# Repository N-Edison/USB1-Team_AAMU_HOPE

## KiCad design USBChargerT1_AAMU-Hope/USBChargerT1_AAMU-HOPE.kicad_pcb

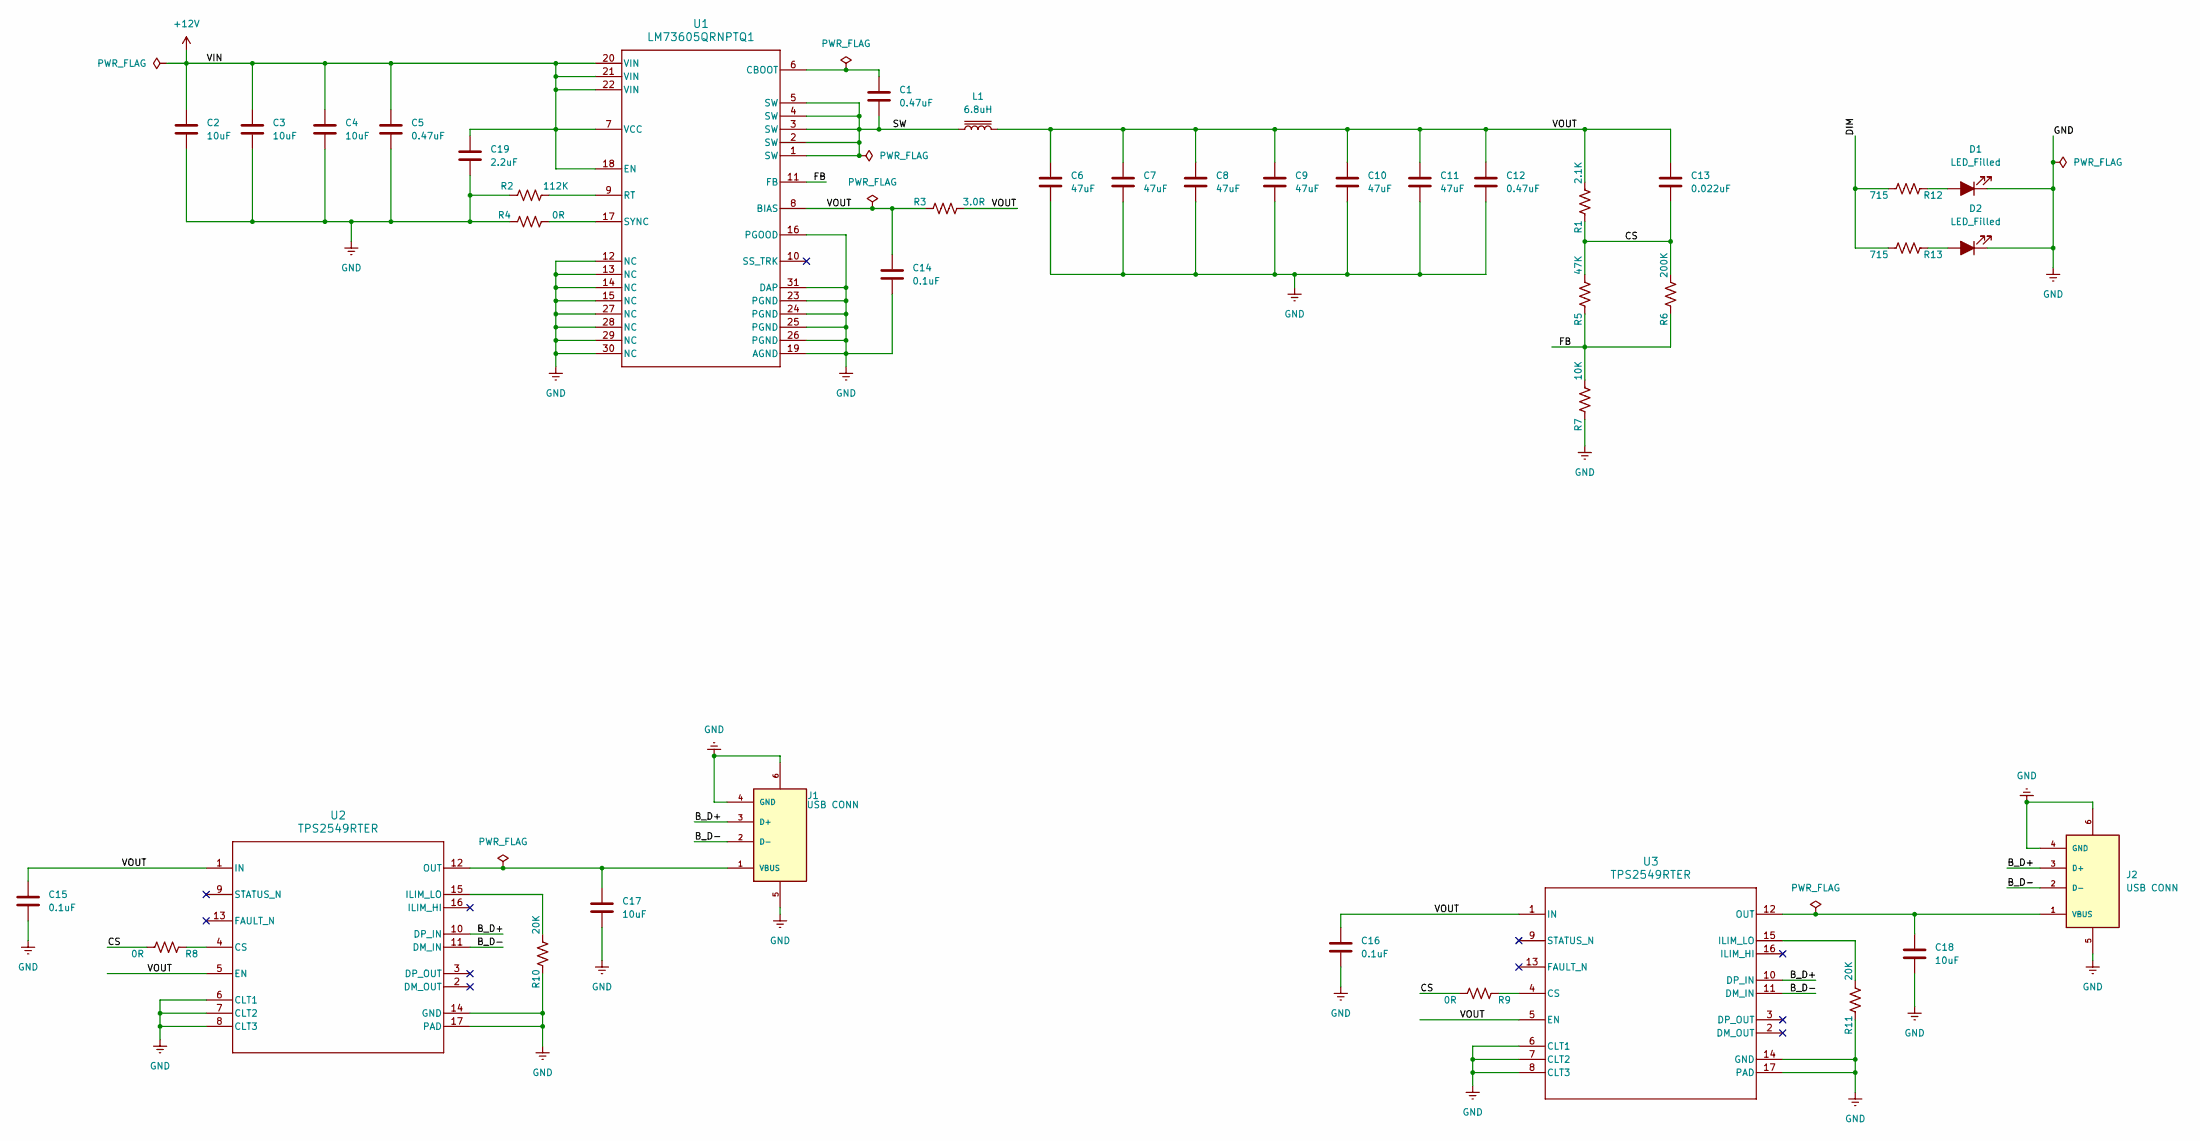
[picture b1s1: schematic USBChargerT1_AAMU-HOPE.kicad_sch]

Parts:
C1, C5, C12: 0.47uF; C_0603_1608Metric_Pad1.08x0.95mm_HandSolder
C2, C3, C4, C17, C18: 10uF; C_0603_1608Metric_Pad1.08x0.95mm_HandSolder
C6, C7, C8, C9, C10, C11: 47uF; C_0603_1608Metric_Pad1.08x0.95mm_HandSolder
C13: 0.022uF; C_0603_1608Metric_Pad1.08x0.95mm_HandSolder
C14, C15, C16: 0.1uF; C_0603_1608Metric_Pad1.08x0.95mm_HandSolder
C19: 2.2uF; C_0603_1608Metric_Pad1.08x0.95mm_HandSolder
D1, D2: LED_Filled; D_0603_1608Metric_Pad1.05x0.95mm_HandSolder
J1, J2: USB CONN; CUI_UJ2-AH-1-SMT; PARTREV 1.01
L1: 6.8uH; L_0603_1608Metric_Pad1.05x0.95mm_HandSolder
R1: 2.1K; R_0603_1608Metric_Pad0.98x0.95mm_HandSolder
R2: 112K; R_0603_1608Metric_Pad0.98x0.95mm_HandSolder
R3: 3.0R; R_0603_1608Metric_Pad0.98x0.95mm_HandSolder
R4, R8, R9: 0R; R_0603_1608Metric_Pad0.98x0.95mm_HandSolder
R5: 47K; R_0603_1608Metric_Pad0.98x0.95mm_HandSolder
R6: 200K; R_0603_1608Metric_Pad0.98x0.95mm_HandSolder
R7: 10K; R_0603_1608Metric_Pad0.98x0.95mm_HandSolder
R10, R11: 20K; R_0603_1608Metric_Pad0.98x0.95mm_HandSolder
R12, R13: 715; R_0603_1608Metric_Pad0.98x0.95mm_HandSolder
U1: LM73605QRNPTQ1; RNP0030A
U2, U3: TPS2549RTER; RTE0016C

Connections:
+12V: C2.1, C3.1, C4.1, C5.1, C19.1, U1.7 (VCC), U1.18 (EN), U1.20 (VIN), U1.21 (VIN), U1.22 (VIN)
/B_D+: J1.3 (D+), J2.3 (D+), U2.10 (DP_IN), U3.10 (DP_IN)
/B_D-: J1.2 (D-), J2.2 (D-), U2.11 (DM_IN), U3.11 (DM_IN)
/CS: C13.2, R1.2, R5.1, R6.1, R8.1, R9.1
/DIM: R12.1, R13.1
/FB: R5.2, R6.2, R7.1, U1.11 (FB)
/SW: C1.2, L1.1, U1.1 (SW), U1.2 (SW), U1.3 (SW), U1.4 (SW), U1.5 (SW)
/VOUT: C6.1, C7.1, C8.1, C9.1, C10.1, C11.1, C12.1, C13.1, C14.1, C15.1, C16.1, L1.2, R1.1, R3.1, R3.2, U1.8 (BIAS), U2.1 (IN), U2.5 (EN), U3.1 (IN), U3.5 (EN)
GND: C2.2, C3.2, C4.2, C5.2, C6.2, C7.2, C8.2, C9.2, C10.2, C11.2, C12.2, C14.2, C15.2, C16.2, C17.2, C18.2, C19.2, D1.1 (K), D2.1 (K), J1.4 (GND), J1.5, J1.6, J2.4 (GND), J2.5, J2.6, R2.2, R4.2, R7.2, R10.2, R11.2, U1.12 (NC), U1.13 (NC), U1.14 (NC), U1.15 (NC), U1.16 (PGOOD), U1.19 (AGND), U1.23 (PGND), U1.24 (PGND), U1.25 (PGND), U1.26 (PGND), U1.27 (NC), U1.28 (NC), U1.29 (NC), U1.30 (NC), U1.31 (DAP), U2.6 (CLT1), U2.7 (CLT2), U2.8 (CLT3), U2.14 (GND), U2.17 (PAD), U3.6 (CLT1), U3.7 (CLT2), U3.8 (CLT3), U3.14 (GND), U3.17 (PAD)
unnamed: D1.2 (A), R12.2
unnamed: D2.2 (A), R13.2
unnamed: C17.1, J1.1 (VBUS), U2.12 (OUT)
unnamed: C18.1, J2.1 (VBUS), U3.12 (OUT)
unnamed: C1.1, U1.6 (CBOOT)
unnamed: R2.1, U1.9 (RT)
unnamed: R4.1, U1.17 (SYNC)
unnamed: R8.2, U2.4 (CS)
unnamed: R10.1, U2.15 (ILIM_LO)
unnamed: R9.2, U3.4 (CS)
unnamed: R11.1, U3.15 (ILIM_LO)

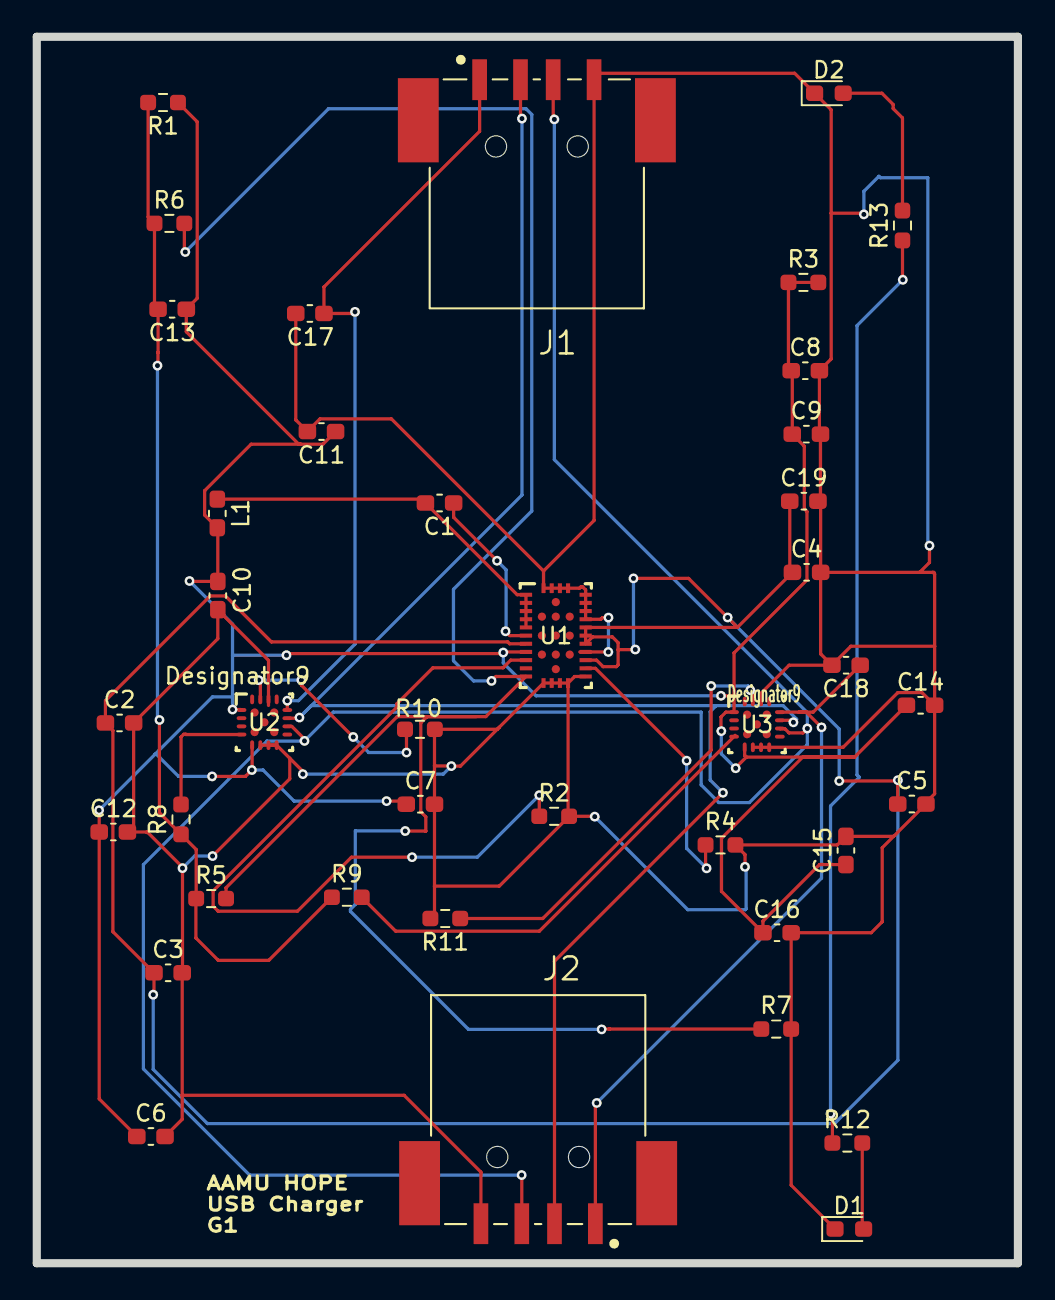
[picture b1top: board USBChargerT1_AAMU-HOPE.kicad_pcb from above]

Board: 2 copper layers, 60.0 x 75.0 mm, 40 parts (0 on the bottom side), 20 nets.

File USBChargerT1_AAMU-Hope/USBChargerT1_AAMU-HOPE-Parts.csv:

Reference,Value,Datasheet,Footprint,Qty,DNP,Link to Parts 
"C1,C5,C12",0.47uF,~,Capacitor_SMD:C_0603_1608Metric_Pad1.08x0.95mm_HandSolder,3,,
"C2,C3,C4,C17,C18",10uF,~,Capacitor_SMD:C_0603_1608Metric_Pad1.08x0.95mm_HandSolder,5,,
"C6,C7,C8,C9,C10,C11",47uF,~,Capacitor_SMD:C_0603_1608Metric_Pad1.08x0.95mm_HandSolder,6,,
C13,0.022uF,~,Capacitor_SMD:C_0603_1608Metric_Pad1.08x0.95mm_HandSolder,1,,
"C14,C15,C16",0.1uF,~,Capacitor_SMD:C_0603_1608Metric_Pad1.08x0.95mm_HandSolder,3,,
C19,2.2uF,~,Capacitor_SMD:C_0603_1608Metric_Pad1.08x0.95mm_HandSolder,1,,
"D1,D2",LED_Filled,~,Diode_SMD:D_0603_1608Metric_Pad1.05x0.95mm_HandSolder,2,,
"J1,J2",USB CONN,,AAMU Senior Design 2024-25:CUI_UJ2-AH-1-SMT,2,,
L1,6.8uH,~,Inductor_SMD:L_0603_1608Metric_Pad1.05x0.95mm_HandSolder,1,,
R1,2.1K,~,Resistor_SMD:R_0603_1608Metric_Pad0.98x0.95mm_HandSolder,1,,
R2,112K,~,Resistor_SMD:R_0603_1608Metric_Pad0.98x0.95mm_HandSolder,1,,
R3,3.0R,~,Resistor_SMD:R_0603_1608Metric_Pad0.98x0.95mm_HandSolder,1,,
"R4,R8,R9",0R,~,Resistor_SMD:R_0603_1608Metric_Pad0.98x0.95mm_HandSolder,3,,
R5,47K,~,Resistor_SMD:R_0603_1608Metric_Pad0.98x0.95mm_HandSolder,1,,
R6,200K,~,Resistor_SMD:R_0603_1608Metric_Pad0.98x0.95mm_HandSolder,1,,
R7,10K,~,Resistor_SMD:R_0603_1608Metric_Pad0.98x0.95mm_HandSolder,1,,
"R10,R11",20K,~,Resistor_SMD:R_0603_1608Metric_Pad0.98x0.95mm_HandSolder,2,,
"R12,R13",715,~,Resistor_SMD:R_0603_1608Metric_Pad0.98x0.95mm_HandSolder,2,,
U1,LM73605QRNPTQ1,LM73605QRNPTQ1,AAMU Senior Design 2024-25:RNP0030A,1,,
"U2,U3",TPS2549RTER,TPS2549RTER,AAMU Senior Design 2024-25:RTE0016C,2,,

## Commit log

2024-11-23 Documentation to perform project
    documentations to perform project for USB Charger KiCad
2024-11-24 TEST RUN OF USB CHARGER PROJECT
    I've tested the project by downloading footprints and symbols and editing symbols. It's still not fully functional and needs work before finishing up. I have folders for symbol and footprint download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
2024-11-24 Finish Schematics and fully functional
    I updated the schematics from U1 (LM73606) to U1 (LM73605), which made the schematics work from the previous results of LM73606. Also, the download to symbol and footprint LM73605 is attached. I also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
2024-11-27 Finished Project
    I ran the DRC(Design Rule Check) on board; everything is wired properly and checks well with no errors. Changed the pad properties on U1, U2, and U3 to SMD Aperture. Also, I changed pads located with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
2024-12-06 More Efficient Design of USB Charger
    More efficient PCB of USB Charger Project from Altium files downloaded from online and transferred to KiCad. The board is fully functional and DRC has been ran with zero errors.
2024-12-06 Update on PCB
    This is an update on PCB USB Charger 1 from Altium files. Still fully functional and working after DRC has been ran on board through KiCad.
2024-12-06 Update on iBom files
    iBom file for USB Charger Altium files turned into KiCad version
    iBom file for USB Charger T1 AAMU HOPE Project
